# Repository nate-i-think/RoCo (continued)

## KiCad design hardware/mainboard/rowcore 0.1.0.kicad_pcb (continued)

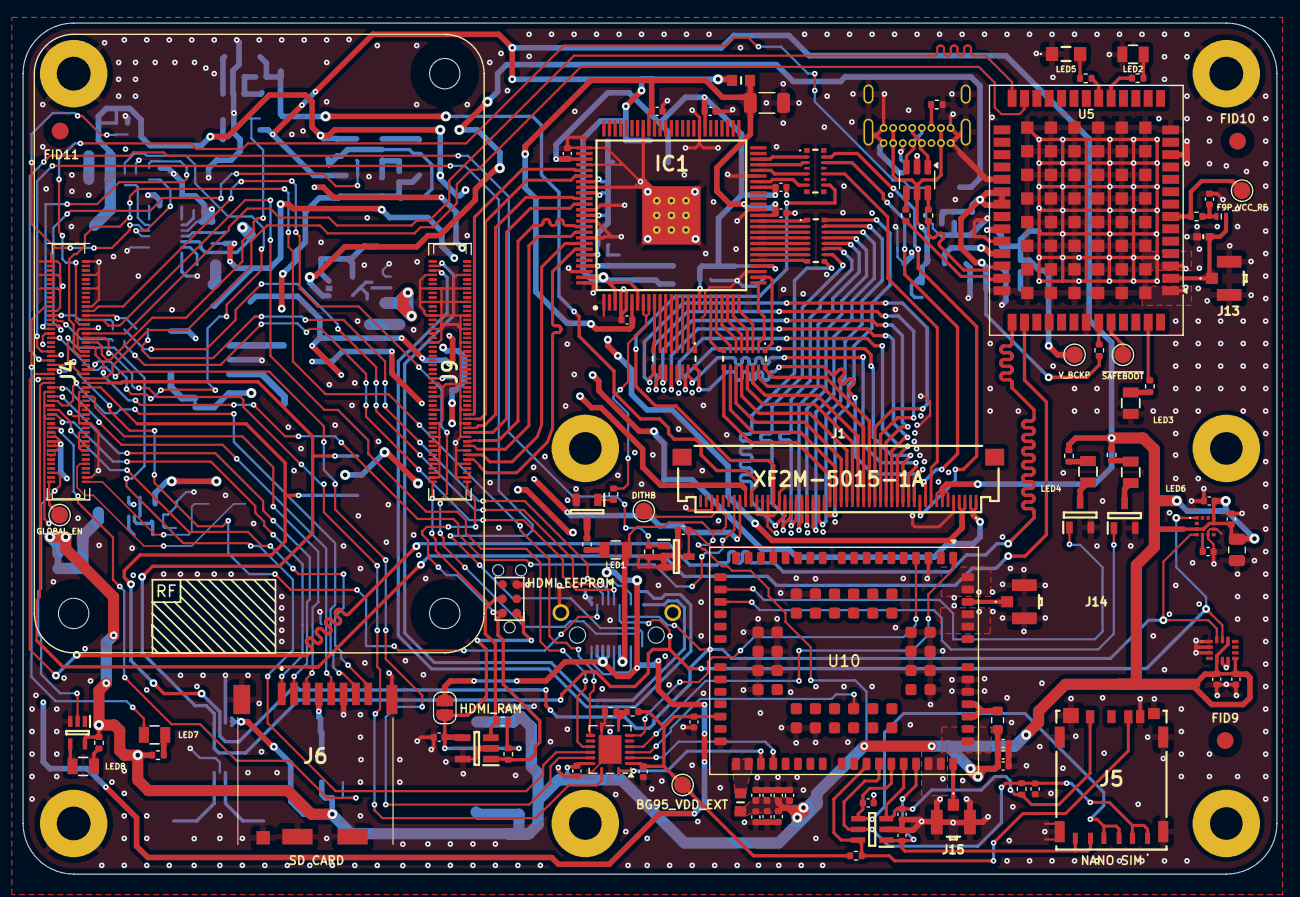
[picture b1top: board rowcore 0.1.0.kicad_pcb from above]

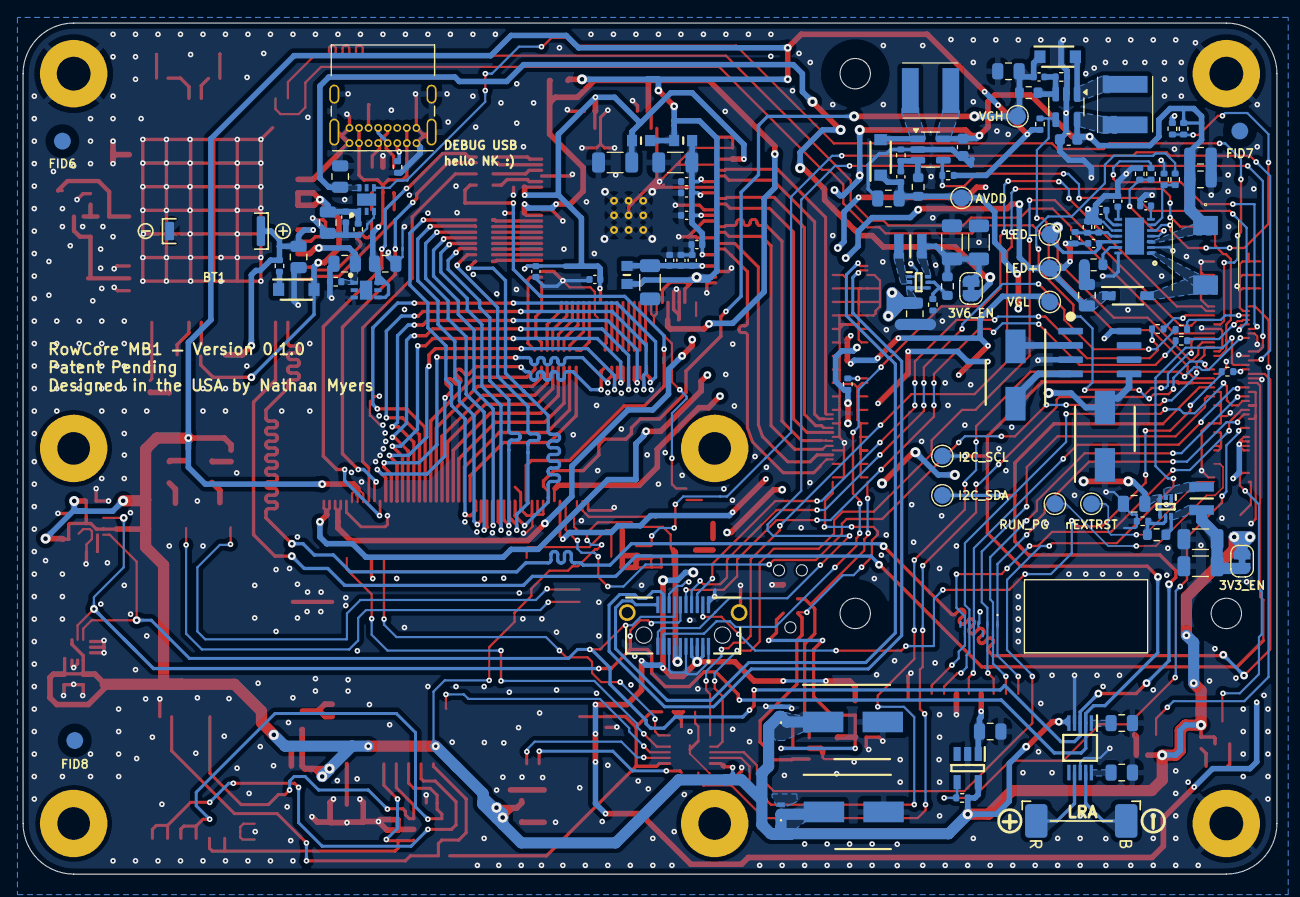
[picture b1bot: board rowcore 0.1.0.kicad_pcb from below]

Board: 4 copper layers, 111.5 x 75.7 mm, 228 parts (117 on the bottom side), 205 nets.

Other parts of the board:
3V3_EN, 3V6_EN: SolderJumper_2_Bridged; SolderJumper-2_P1.3mm_Bridged_RoundedPad1.0x1.5mm
AVDD: AVDD; TestPoint_Pad_D1.5mm
BG95_VDD_EXT: BG_95_VDD_EXT; TestPoint_Pad_D1.5mm
F9P_VCC_RF: VCC_RF; TestPoint_Pad_D1.5mm
GLOBAL_EN: GLOBAL_EN; TestPoint_Pad_D1.5mm
H2#2, H3#2: MountingHole_Pad; MountingHole_3mm_Pad
HDMI_EEPROM: TC2030; Tag-Connect_TC2030-IDC-NL_2x03_P1.27mm_Vertical
HDMI_EN: SolderJumper_2_Open; SolderJumper-2_P1.3mm_Open_RoundedPad1.0x1.5mm
I2C_SCL: I2C_SCL; TestPoint_Pad_D1.5mm
I2C_SDA: I2C_SDA; TestPoint_Pad_D1.5mm
LED+: LED+; TestPoint_Pad_D1.5mm
LED-: LED-; TestPoint_Pad_D1.5mm
RUN_PG: RUN_PG; TestPoint_Pad_D1.5mm
VGH: VGH; TestPoint_Pad_D1.5mm
VGL: VGL; TestPoint_Pad_D1.5mm
V_BCKP: V_BCKP; TestPoint_Pad_D1.5mm
nEXTRST: nEXTRST; TestPoint_Pad_D1.5mm

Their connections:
+3V6: 3V6_EN.2 (B); also elsewhere on the board
+5V: HDMI_EN.1 (A); also elsewhere on the board
/CM4 Lite GPIO/BG95_VDD_EXT: BG95_VDD_EXT.1; also elsewhere on the board
/CM4 Lite GPIO/F9P_VCC_RF: F9P_VCC_RF.1; also elsewhere on the board
/CM4 Lite GPIO/F9P_V_BCKP: V_BCKP.1; also elsewhere on the board
/CM4 Lite GPIO/GLOBAL_EN: GLOBAL_EN.1; also elsewhere on the board
/CM4 Lite GPIO/RUN_PG: RUN_PG.1; also elsewhere on the board
/CM4 Lite GPIO/nEXTRST: nEXTRST.1; also elsewhere on the board
/CM4 Lite High Speed/+5V_HDMI: HDMI_EEPROM.1, HDMI_EN.2 (B); also elsewhere on the board
/CM4 Lite High Speed/DISPLAY_LED+: LED+.1; also elsewhere on the board
/CM4 Lite High Speed/DISPLAY_LED-: LED-.1; also elsewhere on the board
/CM4 Lite High Speed/DISPLAY_VGH_18V: VGH.1; also elsewhere on the board
/CM4 Lite High Speed/DISPLAY_VGL_-10V: VGL.1; also elsewhere on the board
/CM4 Lite High Speed/HDMI_SCL: HDMI_EEPROM.2; also elsewhere on the board
/CM4 Lite High Speed/HDMI_SDA: HDMI_EEPROM.4; also elsewhere on the board
/I2C_SCL: I2C_SCL.1; also elsewhere on the board
/I2C_SDA: I2C_SDA.1; also elsewhere on the board
/Voltage Generation/3v3_out: 3V3_EN.1 (A); also elsewhere on the board
/Voltage Generation/3v6_out: 3V6_EN.1 (A); also elsewhere on the board
/Voltage Generation/DISPLAY_AVDD_10V: AVDD.1; also elsewhere on the board

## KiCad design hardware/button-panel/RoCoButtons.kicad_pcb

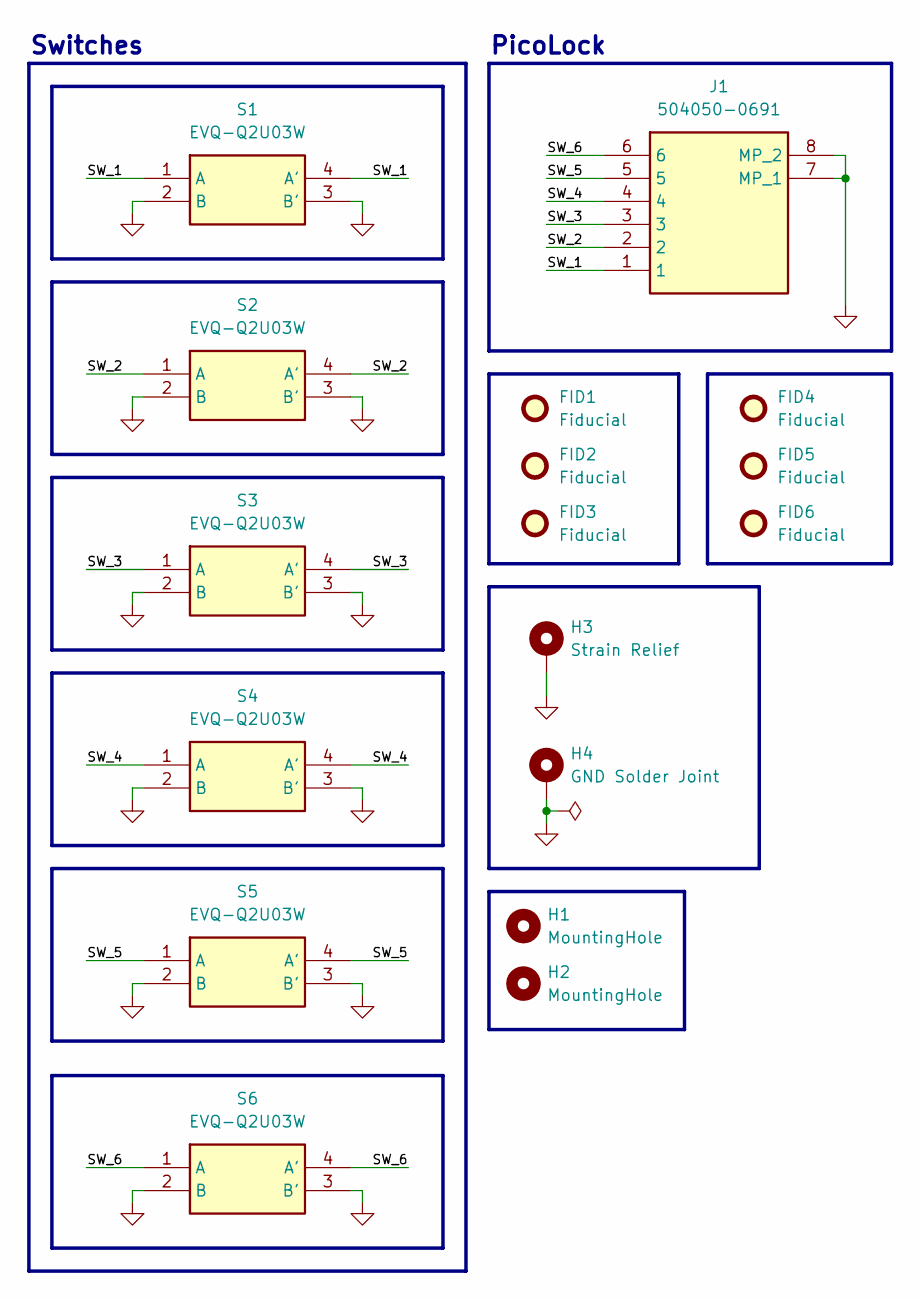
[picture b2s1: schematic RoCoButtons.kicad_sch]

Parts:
FID1, FID2, FID3, FID4, FID5, FID6: Fiducial; Fiducial_0.75mm_Mask1.5mm
H1, H2: MountingHole; MountingHole_2.2mm_M2
H3: Strain Relief; MountingHole_2.2mm_M2_Pad
H4: GND Solder Joint; MountingHole_2.2mm_M2_Pad
J1: 504050-0691; 5040500691; Mouser Part Number 538-504050-0691
S1, S2, S3, S4, S5, S6: EVQ-Q2U03W; EVQQ2; Mouser Part Number 667-EVQ-Q2U03W

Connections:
/SW_1: J1.1, S1.1 (A), S1.4 (A')
/SW_2: J1.2, S2.1 (A), S2.4 (A')
/SW_3: J1.3, S3.1 (A), S3.4 (A')
/SW_4: J1.4, S4.1 (A), S4.4 (A')
/SW_5: J1.5, S5.1 (A), S5.4 (A')
/SW_6: J1.6, S6.1 (A), S6.4 (A')
GND: H3.1, H4.1, J1.7 (MP_1), J1.8 (MP_2), S1.2 (B), S1.3 (B'), S2.2 (B), S2.3 (B'), S3.2 (B), S3.3 (B'), S4.2 (B), S4.3 (B'), S5.2 (B), S5.3 (B'), S6.2 (B), S6.3 (B')

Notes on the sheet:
Switches
PicoLock

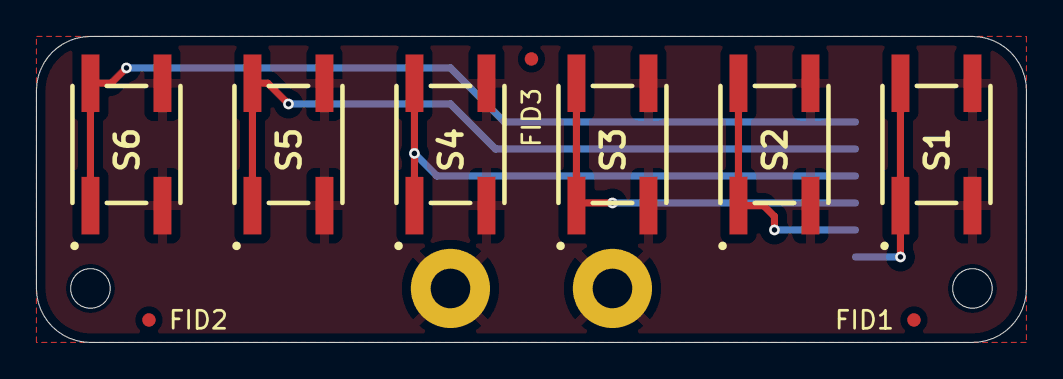
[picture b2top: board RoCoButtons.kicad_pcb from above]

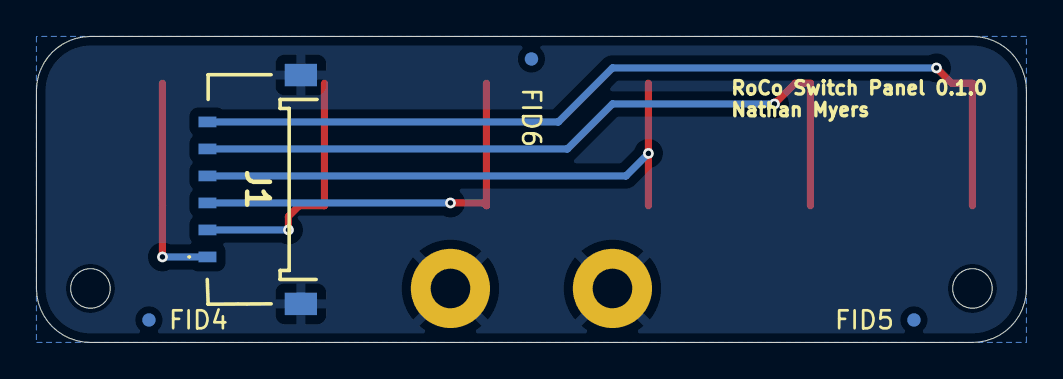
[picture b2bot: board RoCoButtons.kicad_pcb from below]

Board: 2 copper layers, 55.0 x 17.0 mm, 17 parts (4 on the bottom side), 7 nets.

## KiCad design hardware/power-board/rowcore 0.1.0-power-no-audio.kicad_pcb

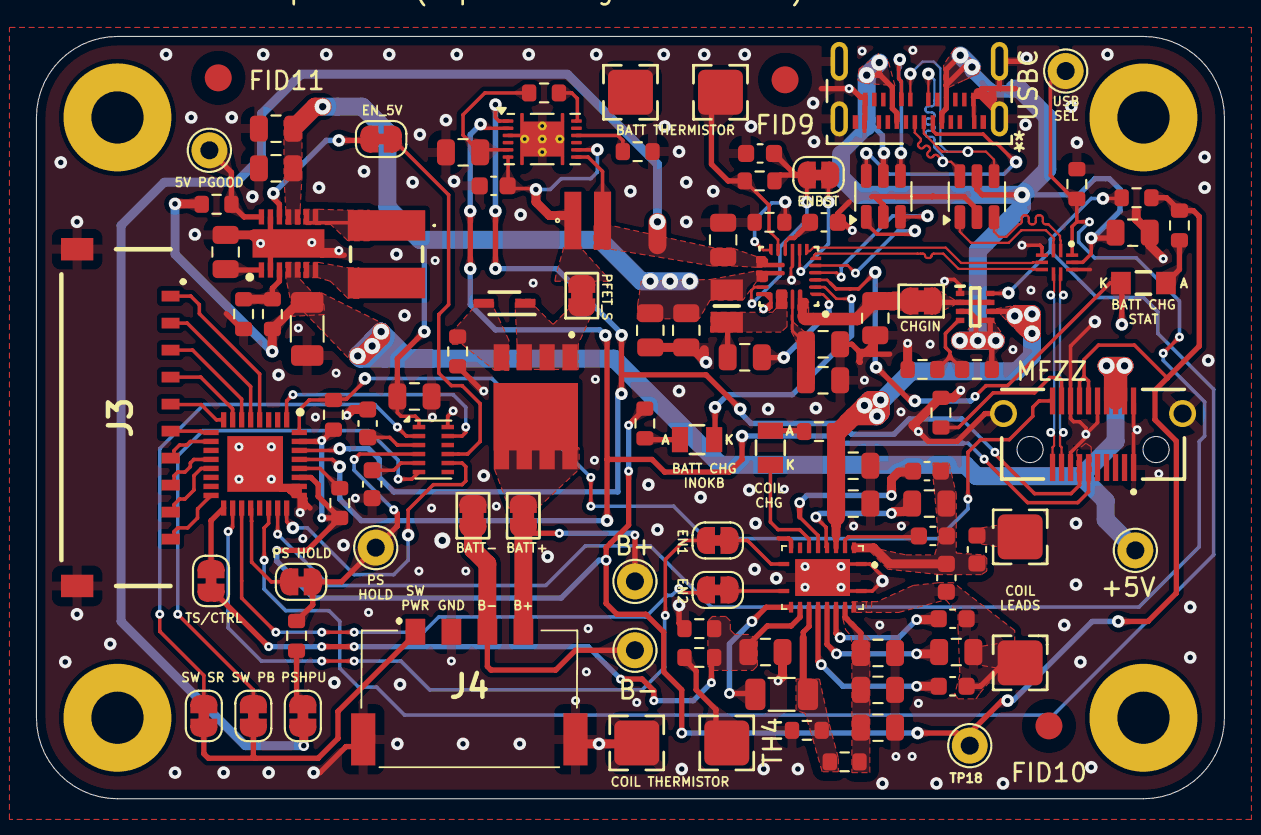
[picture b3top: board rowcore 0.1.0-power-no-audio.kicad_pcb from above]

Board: 4 copper layers, 66.0 x 42.3 mm, 109 parts (0 on the bottom side), 98 nets.

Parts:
C84, C141, C142, C143, C154, C158: 0.1uF; C_0805_2012Metric
C85: 100uF; C_1206_3216Metric
C138, C139, C144, C156, C159, C160, C161, C163, C167, C168: 10uF; C_0805_2012Metric
C140: 10nF; C_0805_2012Metric
C145, C150: 0.47uF_25V; C_0805_2012Metric
C146, C149: 33nF_25V; C_0603_1608Metric
C147, C148: 10nF_25V; C_0603_1608Metric
C151: 150nF; C_0603_1608Metric
C152, C157, C165: 2.2uF; C_0603_1608Metric
C153, C155: 1uF; C_0603_1608Metric
C162: 1.0uF; C_0603_1608Metric
C164: 22uF; C_0805_2012Metric
C166: 0.47uF; C_0805_2012Metric
FID9, FID10, FID11: Fiducial; Fiducial_1.5mm_Mask3mm
H1, H2, H3, H4: MountingHole_Pad; MountingHole_3mm_Pad
IC10: PCAL6524HEAZ; QFN50P500X500X60-33N-D
IC11: RT6154AGQW; SON50P300X400X80-15N-D
IC16: BQ51013BRHLR; BQ51050BRHLR
IC17: PI3USB102GZLEX; QFN40P130X160X80-10N
IC18: TPS2117DRLR; SOTFL50P160X60-8N
J3: 504050-1091; 5040501091
J4: 205338-0004; 2053380004
J7: LSHM-110-02.5-L-DV-A-S-K-TR; SAMTEC_LSHM-110-02.5-L-DV-A-S-K-TR
J13: USB_C_124018802112A; 124018802112A_AMP
JP7, JP8, JP37, JP39: SolderJumper_2_Bridged; SolderJumper-2_P3.0mm_Bridged_Pad
JP28, JP29, JP30, JP33, JP34, JP35, JP36, JP38, JP40: SolderJumper_2_Bridged; SolderJumper-2_P1.3mm_Bridged_RoundedPad1.0x1.5mm
L6: 0.47uH; INDC2016X80N
L9: 12uH; QiCoilPads
L10: 2.2uH; LLEUB4040WKT2R2M
LED15, LED17: LO_R976-PS-1; LEDC2012X90N
LED16: LTST-C171KSKT; LTSTC171KSKT
Q9: TPH1R712MD,L1Q; TPH1R712MDL1Q
R43, R46, R47, R89, R91, R93, R98, R99, R100: 10k; R_0603_1608Metric
R49: 66R_1%; R_1206_3216Metric
R53, R54, R90, R92: 100k; R_0603_1608Metric
R55: 1.8M_1%; R_0603_1608Metric
R56: 200k_1%; R_0603_1608Metric
R80: 20k; R_0603_1608Metric
R85, R101: 2.55k_1%; R_0603_1608Metric
R86: 196R_1%; R_0603_1608Metric
R87: 106k_1%; R_0603_1608Metric
R94, R95: 1k; R_0603_1608Metric
R96: 22.6k_1%; R_0603_1608Metric
R97: 0.010R_1%; ERJD2
TH4, TH5: 10k; 103AT-4-10228
TP6: PGOOD; TestPoint_THTPad_D2.0mm_Drill1.0mm
TP12: +5V; TestPoint_THTPad_D2.0mm_Drill1.0mm
TP17: SEL; TestPoint_THTPad_D2.0mm_Drill1.0mm
TP18: 3v3; TestPoint_THTPad_D2.0mm_Drill1.0mm
TP20: PS_HOLD; TestPoint_THTPad_D2.0mm_Drill1.0mm
TP21: BATT+; TestPoint_THTPad_D2.0mm_Drill1.0mm
TP22: BATT-; TestPoint_THTPad_D2.0mm_Drill1.0mm
U18, U22: USBLC6-2SC6; SOT-23-6
U19: STM6601CA2BDM6F; TDFN-12_2x3mm_P0.5mm
U20: MAX77757
U21: BQ27441DRZR-G1A; Texas_S-PDSO-N12
Z3: BZX384-C8V2,115; SOD2512X110N

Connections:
+3V3: IC10.27 (VDD(P)), IC10.31 (VDD(I2C-BUS)), J7.12, J7.14, R46.1, R47.1, R93.1, R94.1, R95.1, TP18.1
+5V: C85.1, IC11.4 (VOUT_1), IC11.5 (VOUT_2), J7.04, J7.06, J7.08, R54.2, R55.1, TP12.1
+5V_WIRELESS: C143.1, C144.1, IC16.4 (OUT), IC18.6 (VIN2), R101.2
+BATT: C160.1, JP34.2 (B), R97.2, U20.13 (BATT), U20.14 (BATT), U21.7 (SRN)
+PWR_IN: IC18.2 (VOUT_1), IC18.7 (VOUT_2), JP37.1 (A)
+SYS: C154.1, C159.1, C163.1, C167.1, C168.1, IC11.10 (VIN_1), IC11.11 (VIN_2), L6.2, U19.1 (Vcc), U20.15 (SYS), U20.16 (SYS)
+USB_V_{BUS}: C142.1, IC17.9 (VDD), IC18.3 (VIN1), IC18.5 (MODE), J13.A4 (V_{BUS}), J13.A9 (V_{BUS}), J13.B4 (V_{BUS}), J13.B9 (V_{BUS}), R91.1, U18.5 (VBUS), U22.5 (VBUS)
/5V_PGOOD: IC11.14 (PGOOD), R54.1, TP6.1
/6601_C_SRD: C153.1, U19.5 (C_SRD)
/77737_VDD: C157.1, U20.10 (VDD)
/AC1: C145.2, C146.2, C147.2, C151.1, C152.1, IC16.2 (AC1)
/AC1_out: C152.2, L9.1
/AC2: C148.2, C149.2, C150.2, C151.2, IC16.19 (AC2), L9.2
/BATT+_out: J4.4, JP7.1 (A), TP21.1
/BATT-_out: J4.3, JP8.1 (A), TP22.1
/BATT_+: C162.1, JP39.2 (B), R97.1, U21.6 (BAT), U21.8 (SRP)
/BATT_THERMISTOR: R98.1, TH5.1, U20.11 (THM)
/BIN: R99.1, U21.10 (BIN)
/BOARD_ID: J7.18, R43.1
/BOOT1: C147.1, IC16.3 (BOOT1)
/BOOT2: C148.1, IC16.17 (BOOT2)
/BQ27441_GPOUT: R100.2, U21.12 (GPOUT)
/BQ27441_VDD: C166.1, R100.1, U21.5 (V_{DD})
/BST: C158.1, U20.1 (BST)
/BYP: C161.1, C164.1, U20.22 (BYP)
/CHGIN: C156.1, JP37.2 (B), U20.23 (CHGIN), U20.24 (CHGIN)
/CHG_LED: IC16.7 (~CHG), LED15.1 (K)
/CHG_LED_R: LED15.2 (A), R101.1
/CLAMP1: C145.1, IC16.5 (CLAMP1)
/CLAMP2: C150.1, IC16.16 (CLAMP2)
/COMM1: C146.1, IC16.6 (COMM1)
/COMM2: C149.1, IC16.15 (COMM2)
/EN1: IC16.10 (EN1), JP28.2 (B)
/EN2: IC16.11 (EN2), JP29.2 (B)
/ENBST: JP38.2 (B), U20.8 (ENBST)
/EN_5V: JP40.1 (A), U19.9 (~EN/EN)
/EN_5V_J: IC11.12 (EN), JP40.2 (B)
/FB: IC11.3 (FB), R55.2, R56.1
/FOD: IC16.14 (FOD), R49.1, R80.2, R86.1
/GPIO_EXP_~INT: IC10.32 (~INT), J7.20, R47.2
/GPIO_~RESET: IC10.28 (~RESET), R46.2
/I2C_SCL: IC10.29 (SCL), J7.11, U21.2 (SCL)
/I2C_SDA: IC10.30 (SDA), J7.13, U21.1 (SDA)
/IFAST: R96.1, U20.12 (IFAST)
/ILIM: IC16.12 (ILIM), R49.2
/INOKB: LED17.1 (K), U20.2 (INOKB)
/INOKB_LED: LED17.2 (A), R94.2
/LX: C158.2, L6.1, U20.20 (LX), U20.21 (LX)
/P0_0: IC10.1 (P0_0), U19.11 (~INT)
/P0_3: IC10.4 (P0_3), J3.1
/P0_4: IC10.5 (P0_4), J3.2
/P0_5: IC10.6 (P0_5), J3.3
/P0_6: IC10.7 (P0_6), J3.4
/P0_7: IC10.8 (P0_7), J3.5
/P1_0: IC10.9 (P1_0), J3.6
/P1_1: IC10.10 (P1_1), J3.7
/P1_3: IC10.12 (P1_3), J3.8
/P1_4: IC10.13 (P1_4), J3.9
/P1_7: IC10.16 (P1_7), J3.10
/P2_0: IC10.17 (P2_0), JP30.1 (A)
/P2_1: IC10.18 (P2_1), JP28.1 (A)
/P2_2: IC10.19 (P2_2), JP29.1 (A)
/P2_3: IC10.20 (P2_3), JP33.1 (A)
/P2_5: IC10.22 (P2_5), IC18.8 (ST), R93.2
/P2_6: IC10.23 (P2_6), IC17.10 (SEL), R89.1, TP17.1
/PB: JP36.1 (A), U19.6 (~PB)
/PROT_PFET_D: JP7.2 (B), Q9.5 (D_1), Q9.6 (D_2), Q9.7 (D_3), Q9.8 (D_4), Q9.9 (D_5)
/PROT_PFET_G: Q9.4 (G), R53.1, Z3.2 (A)
/PROT_PFET_S: JP39.1 (A), Q9.1 (S_1), Q9.2 (S_2), Q9.3 (S_3), Z3.1 (K)
/PS_HOLD: JP33.2 (B), R90.2, TP20.1, U19.4 (PS_HOLD)
/PS_HOLD_PU: JP34.1 (A), R90.1
/PVL: C165.1, JP38.1 (A), R98.2, U20.17 (PVL)
/PWR_OR_PR1: IC18.4 (PR1), R91.2, R92.1
/PWR_PB_OUT: IC10.24 (P2_7), U19.8 (~PB_OUT)
/RECT: C138.2, C139.2, C141.2, IC16.18 (RECT), R80.1
/SR: JP35.2 (B), U19.2 (~SR)
/STAT: LED16.1 (K), U20.3 (STAT)
/STAT_LED: LED16.2 (A), R95.2
/SW_1: IC11.8 (SW1_1), IC11.9 (SW1_2), L10.1
/SW_2: IC11.6 (SW2_1), IC11.7 (SW2_2), L10.2
/Switch_PWR: J4.1, JP35.1 (A), JP36.2 (B)
/TS/CTRL: C140.1, IC16.13 (TS/CTRL), JP30.2 (B), R85.1, R87.1
/TS/CTRL_r1: R85.2, TH4.1
/USB_CC1: U20.5 (CC1), U22.1 (I/O1)
/USB_CC1_c: J13.A5 (CC1), U22.6 (I/O1)
/USB_CC2: U20.4 (CC2), U22.3 (I/O2)
/USB_CC2_c: J13.B5 (CC2), U22.4 (I/O2)
/USB_D+: IC17.1 (Y+), U18.3 (I/O2)
/USB_D-: IC17.2 (Y-), U18.1 (I/O1)
/USB_DATA_D+: IC17.7 (D+), J7.17
/USB_DATA_D-: IC17.6 (D-), J7.19
/USB_PD_D+: IC17.5 (M+), U20.6 (DP)
/USB_PD_D-: IC17.4 (M-), U20.7 (DN)
/USB_c_D+: J13.A6 (D+), J13.B6 (D+), U18.4 (I/O2)
/USB_c_D-: J13.A7 (D-), J13.B7 (D-), U18.6 (I/O1)
/VIN_A: C84.1, IC11.1 (VINA)
/V_{REF}: C155.1, U19.3 (Vref)
GND: C84.2, C85.2, C138.1, C139.1, C140.2, C141.1, C142.2, C143.2, C144.2, C153.2, C154.2, C155.2, C156.2, C157.2, C159.2, C160.2, C161.2, C162.2, C163.2, C164.2, C165.2, C166.2, C167.2, C168.2, IC10.25 (VSS), IC10.26 (ADDR), IC10.33 (EP), IC11.2 (GND), IC11.13 (PS/SYNC), IC11.15 (PGND), IC16.1 (PGND_1), IC16.9 (AD), IC16.20 (PGND_2), IC16.21 (EP), IC17.3 (GND), IC17.8 (~OE), IC18.1 (GND), J3.MP1, J3.MP2, J4.2, J4.MP1, J4.MP2, J7.01, J7.02, J7.10, J7.15, J7.16, J7.S1 (SHIELD), J7.S2 (SHIELD__1), J13.A1 (GND), J13.A12 (GND), J13.B1 (GND), J13.B12 (GND), J13.SHEILD, JP8.2 (B), R43.2, R53.2, R56.2, R86.2, R87.2, R89.2, R92.2, R96.2, R99.2, TH4.2, TH5.2, U18.2 (GND), U19.12 (GND), U20.9 (GND), U20.18 (PGND), U20.19 (PGND), U21.3 (V_{SS}), U21.13 (PAD), U22.2 (GND)

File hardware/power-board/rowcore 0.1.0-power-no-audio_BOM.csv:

Qty,Reference(s),Value,Footprint,Manufacturer,Manufacturer Part Number
6,"C84, C141, C142, C143, C154, C158",0.1uF,Capacitor_SMD:C_0805_2012Metric,~,~
1,C85,100uF,Capacitor_SMD:C_1206_3216Metric,~,~
10,"C138, C139, C144, C156, C159, C160, C161, C163, C167, C168",10uF,Capacitor_SMD:C_0805_2012Metric,~,~
1,C140,10nF,Capacitor_SMD:C_0805_2012Metric,~,~
2,"C145, C150",0.47uF_25V,Capacitor_SMD:C_0805_2012Metric,~,~
2,"C146, C149",33nF_25V,Capacitor_SMD:C_0603_1608Metric,~,~
2,"C147, C148",10nF_25V,Capacitor_SMD:C_0603_1608Metric,~,~
1,C151,150nF,Capacitor_SMD:C_0603_1608Metric,~,~
3,"C152, C157, C165",2.2uF,Capacitor_SMD:C_0603_1608Metric,~,~
2,"C153, C155",1uF,Capacitor_SMD:C_0603_1608Metric,~,~
1,C162,1.0uF,Capacitor_SMD:C_0603_1608Metric,~,~
1,C164,22uF,Capacitor_SMD:C_0805_2012Metric,~,~
1,C166,0.47uF,Capacitor_SMD:C_0805_2012Metric,~,~
1,IC10,PCAL6524HEAZ,SamacSys_Parts:QFN50P500X500X60-33N-D,NXP,PCAL6524HEAZ
1,IC11,RT6154AGQW,SamacSys_Parts:SON50P300X400X80-15N-D,RICHTEK,RT6154AGQW
1,IC16,BQ51013BRHLR,SamacSys_Parts:BQ51050BRHLR,Texas Instruments,BQ51013BRHLR
1,IC17,PI3USB102GZLEX,SamacSys_Parts:QFN40P130X160X80-10N,Diodes Incorporated,PI3USB102GZLEX
1,IC18,TPS2117DRLR,SamacSys_Parts:SOTFL50P160X60-8N,Texas Instruments,TPS2117DRLR
1,J3,504050-1091,5040501091,Molex,504050-1091
1,J4,205338-0004,2053380004,Molex,205338-0004
1,J7,LSHM-110-02.5-L-DV-A-S-K-TR,LSHM-110-02.5-L-DV-A-S-K-TR:SAMTEC_LSHM-110-02.5-L-DV-A-S-K-TR,Samtec,LSHM-110-02.5-L-DV-A-S-K-TR 
1,J13,USB_C_124018802112A,124018802112A:124018802112A_AMP,Amphenol Commercial Products,124018802112A 
1,L6,0.47uH,SamacSys_Parts:INDC2016X80N,SAMSUNG,CIGT201610EHR47MNE
1,L10,2.2uH,SamacSys_Parts:LLEUB4040WKT2R2M,TAIYO YUDEN,LLEUB4040WKT2R2M
2,"LED15, LED17",LO_R976-PS-1,SamacSys_Parts:LEDC2012X90N,ams OSRAM,LO R976-PS-1
1,LED16,LTST-C171KSKT,SamacSys_Parts:LTSTC171KSKT,Lite-On,LTST-C171KSKT
1,Q9,"TPH1R712MD,L1Q",SamacSys_Parts:TPH1R712MDL1Q,Toshiba,"TPH1R712MD,L1Q"
9,"R43, R46, R47, R89, R91, R93, R98, R99, R100",10k,Resistor_SMD:R_0603_1608Metric,~,~
1,R49,66R_1%,Resistor_SMD:R_1206_3216Metric,YAGEO, RC1206FR-0766R5L
4,"R53, R54, R90, R92",100k,Resistor_SMD:R_0603_1608Metric,~,~
1,R55,1.8M_1%,Resistor_SMD:R_0603_1608Metric,YAGEO,AC0603FR-071M8L 
1,R56,200k_1%,Resistor_SMD:R_0603_1608Metric,~,~
1,R80,20k,Resistor_SMD:R_0603_1608Metric,~,~
2,"R85, R101",2.55k_1%,Resistor_SMD:R_0603_1608Metric,YAGEO,RC0603FR-072K55L
1,R86,196R_1%,Resistor_SMD:R_0603_1608Metric,Vishay,CRCW0603196RFKEA
1,R87,106k_1%,Resistor_SMD:R_0603_1608Metric,Panasonic,ERJ-3EKF1073V
2,"R94, R95",1k,Resistor_SMD:R_0603_1608Metric,~,~
1,R96,22.6k_1%,Resistor_SMD:R_0603_1608Metric,YAGEO, RC0603FR-1022K6L
1,R97,0.010R_1%,SamacSys_Parts:ERJD2,Panasonic ,ERJ-D2DFR010V
2,"U18, U22",USBLC6-2SC6,Package_TO_SOT_SMD:SOT-23-6,STMicroelectronics,USBLC6-2SC6 
1,U19,STM6601CA2BDM6F,Package_DFN_QFN:TDFN-12_2x3mm_P0.5mm,STMicroelectronics ,STM6601CA2BDM6F
1,U20,MAX77757,MAX77757:MAX77757,Analog Devices / Maxim Integrated,MAX77757JEFG435+
1,U21,BQ27441DRZR-G1A,Package_SON:Texas_S-PDSO-N12,,
1,Z3,"BZX384-C8V2,115",SamacSys_Parts:SOD2512X110N,Nexperia,"BZX384-C8V2,115"

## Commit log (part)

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2025-07-03 libraries: CM4IO symbol + io connector footprints
2025-07-09 libraries: MP3308 backlight driver and ICL7660S charge pump
2025-07-15 libraries: MS621R coin cell footprint
2025-07-23 libraries: haptic motor pad symbol
2025-07-25 libraries: qi coil pads
2025-07-27 libraries: usb-c receptacle footprints (124018802112A)
2025-07-30 libraries: 103AT ntc thermistor
2025-08-02 mainboard: io, battery and power sheet
2025-08-02 libraries: Samtec LSHM board-to-board connectors
2025-08-06 libraries: LSHM-110 footprint
2025-08-21 libraries: MAX77757 charger symbol
2025-08-24 libraries: add MAX77757 footprint, usb-c symbol (124018802112A) and 3mm solder jumper
2025-08-26 mainboard: daughter board sheet + empty voice variant
2025-08-27 power-board: schematic (usb-c charger, qi receiver, fuel gauge, buck-boost)
2025-09-02 libraries: VG1030001XH haptic pad footprint
2025-09-04 mainboard: project library tables
2025-09-04 libraries: CM4 module footprint
2025-09-06 enclosure: board alignment test
2025-09-07 mainboard: netlist and bom export
2025-09-07 mainboard: root, cm4-gpio, cm4-high-speed, power + assorted sheets
2025-09-18 mainboard: fab readme, stackup, renders and bom
2025-09-18 power-board: v0.1.0 layout for fab
2025-09-18 mainboard: impedance control specifics
2025-09-18 power-board: gerber plot layer selection
2025-09-19 mainboard: fab outputs (gerbers, drill, impedance spec)
2025-11-19 mainboard: board layout (earliest surviving revision)
2025-12-01 power-board: v0.2.0 reroute, Pico-Lock connectors, new fab outputs
2025-12-08 mainboard: project settings
2025-12-30 enclosure: case prototype 1
2026-01-02 mainboard: wireless keepout on all copper layers, refresh teardrops
2026-01-03 button-panel: new project, schematic
2026-01-03 power-board: silkscreen note to fix usb impedance
2026-01-03 ufl-adapter: schematic, layout and fab outputs
2026-01-03 button-panel: layout, gerbers, bom and cpl
2026-01-04 enclosure: case prototype 1 rework, proto 2 print exports
2026-01-05 power-board: move usb-c label on schematic
2026-01-05 enclosure: proto 2 display bracket
2026-01-05 Major toolchain refactor
2026-01-06 enclosure: proto 2 power board pegs
2026-01-10 Preliminary working DRM/KMS setup, midway through being moved into its own file display.rs.
2026-01-10 Compartmentalize and finalize KMS/DRM rendering system and Add text rendering system.
2026-01-12 draft of debug terminal setup + colored text + many rendering changes
2026-01-12 fully working debug terminal
2026-01-12 untested beginnings of gps handle and start of appcontext
2026-01-12 enormous additions and refactor of ubx.rs
2026-01-12 further revisions to ubx.rs, finishing the plumbing
2026-01-14 enormous changes to the GPS system—fully gorgeously async now with a system that manages slow packet delivery, etc., very well.
2026-01-15 enclosure: proto 3 exports (top shell, brackets, peg, aligner tab)
2026-01-15 enclosure: case prototype 2, tpu button cover
2026-01-18 mainboard: refill zones
2026-01-22 mainboard: move usim interface label
2026-01-26 last commit before integrating Claude Code
2026-01-26 fix ubx.rs bugs and refactor routes to hashmap
    - fix nav-pvt carrier_solution parsing (1/2 were swapped)
    - fix cfg-valget position indices ([3,4] -> [2,3])
    - fix cfg_valget_incoming missing bounds check
    - replace println! with tracing::debug! using proper targets
    - refactor UBXHubInner.routes from 65K OnceLock array to parking_lot::RwLock<HashMap>
    - fix comment typos
2026-01-26 rewrite claude.md to be succinct and add learnings
2026-01-27 added AT parsing (at.rs) and cell.rs for nice handling, similar to how ubx.rs and gps.rs are paired together. untested as of now.
2026-02-17 mainboard: board color tweak in project settings
2026-03-22 mainboard: nudge section frame on cm4-gpio sheet
